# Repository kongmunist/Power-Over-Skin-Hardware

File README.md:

# Hi, welcome to the Power-over-Skin Repo

This repository contains the PCB files for the receiver board from the ACM UIST paper ["Power-over-Skin: Full-Body Wearables Powered By Intra-Body RF Energy"](https://dl.acm.org/doi/10.1145/3654777.3676394)

# BOM for receiver
You can assume all parts are generic unless mentioned below:

- R1-R7: Voltage setting resistors, should be 1% or better

- L2, L3: buck/boost inductors for the BQ25570. Should handle >200mA saturation current according to BQ25570 datasheet, but we're using low currents so you would probably get away with lower values. We used CB2518T100K and BRC2518T220K

- C4: Anything >100uF will do. I'm using the F950J107MPAAQ2, it is the only one that's quite so small, but it's also very DC-leaky

- L1: Should have a self-resonant frequency over 200 MHz in order to accomodate incoming square wave harmonics. 
- C9: Should be NP0, with a Vmax 10V or better

# Transmitter
In our experiments, we used a benchtop transmitter and a wearable one to generate 40 MHz square waves. These were passed through an impedance-matching network to couple into the body. The values we used were: first 20pF in series, then 820nH to ground. 

The 20pF should be NP0 with a voltage rating higher than the 40MHz you're sending into it. We used this inductor [(L-15FR82JV4E)](https://www.mouser.com/ProductDetail/Johanson-Technology/L-15FR82JV4E?qs=N%252Bgu1CRRfTPf9IhMOTDbHA%3D%3D) but anything with a self-resonant frequency >200 MHz should work. 

# Matching for other frequencies
The RF component values are all tuned for 40 MHz and human skin impedance — if you'd like to use another frequency, you'll have to resimulate the circuit. 

# Further questions?
Feel free to email Andy with any questions!

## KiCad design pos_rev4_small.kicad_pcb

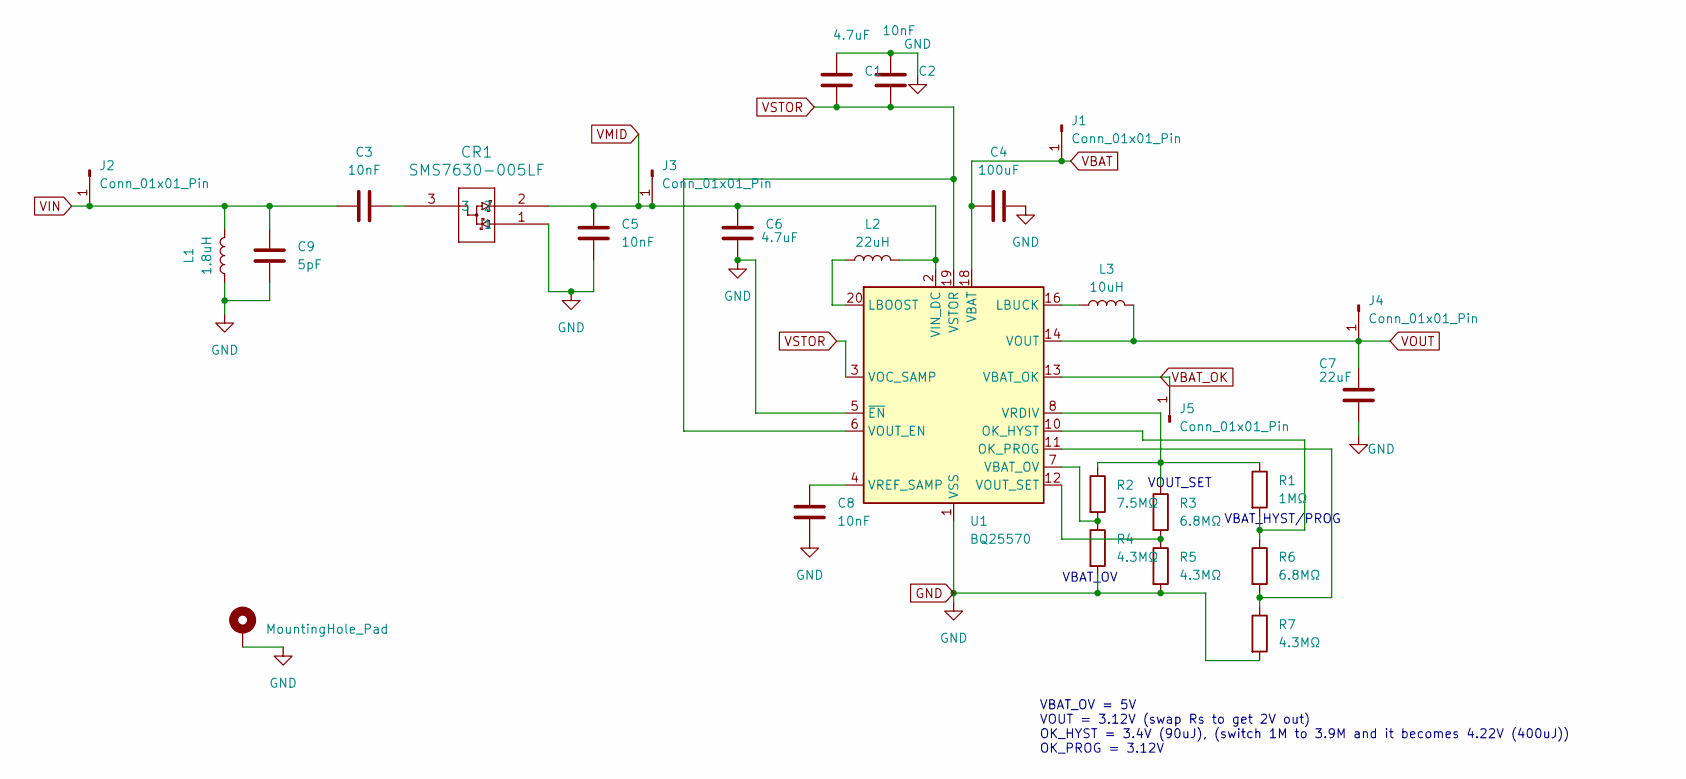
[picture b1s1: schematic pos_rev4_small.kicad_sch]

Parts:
C1, C6: 4.7uF; C_0402_1005Metric
C2, C3, C5, C8: 10nF; C_0402_1005Metric
C4: 100uF; C_0805_2012Metric
C7: 22uF; C_0603_1608Metric
C9: 5pF; C_0402_1005Metric
CR1: SMS7630-005LF; SOT-23_SKY
H1: MountingHole_Pad; TestPoint_Pad_D1.0mm
J1, J2, J3, J4, J5: Conn_01x01_Pin; TestPoint_Pad_D1.0mm
L1: 1.8uH; L_0805_2012Metric
L2: 22uH; L_1008_2520Metric
L3: 10uH; L_0805_2012Metric
R1: 1MΩ; R_0402_1005Metric
R2: 7.5MΩ; R_0402_1005Metric
R3, R6: 6.8MΩ; R_0402_1005Metric
R4, R5, R7: 4.3MΩ; R_0402_1005Metric
U1: BQ25570; QFN-20-1EP_3.5x3.5mm_P0.5mm_EP2x2mm

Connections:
GND: C1.1, C2.1, C4.2, C5.1, C6.2, C7.2, C8.2, C9.1, CR1.1, H1.1, L1.2, R4.2, R5.2, R7.2, U1.1 (VSS), U1.5 (~EN), U1.9 (VSS), U1.15 (VSS), U1.17 (VSS), U1.21 (VSS)
unnamed: C3.2, CR1.3
unnamed: L2.1, U1.20 (LBOOST)
unnamed: L3.1, U1.16 (LBUCK)
unnamed: R1.2, R6.1, U1.10 (OK_HYST)
unnamed: R6.2, R7.1, U1.11 (OK_PROG)
unnamed: R2.2, R4.1, U1.7 (VBAT_OV)
unnamed: R3.2, R5.1, U1.12 (VOUT_SET)
unnamed: R1.1, R2.1, R3.1, U1.8 (VRDIV)
unnamed: C8.1, U1.4 (VREF_SAMP)
VBAT: C4.1, J1.1, U1.18 (VBAT)
VBAT_OK: J5.1, U1.13 (VBAT_OK)
VIN: C3.1, C9.2, J2.1, L1.1
VMID: C5.2, C6.1, CR1.2, J3.1, L2.2, U1.2 (VIN_DC)
VOUT: C7.1, J4.1, L3.2, U1.14 (VOUT)
VSTOR: C1.2, C2.2, U1.3 (VOC_SAMP), U1.6 (VOUT_EN), U1.19 (VSTOR)

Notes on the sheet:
VOUT_SET
VBAT_HYST/PROG
VBAT_OV
VBAT_OV = 5V VOUT = 3.12V (swap Rs to get 2V out) OK_HYST = 3.4V (90uJ), (switch 1M to 3.9M and it becomes 4.22V (400uJ)) OK_PROG = 3.12V

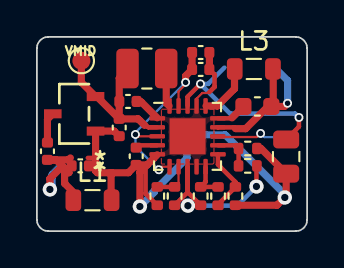
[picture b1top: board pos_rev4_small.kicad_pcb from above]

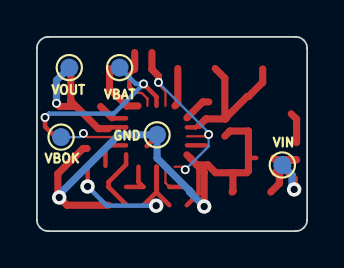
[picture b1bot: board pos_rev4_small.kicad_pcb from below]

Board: 2 copper layers, 15.0 x 10.8 mm, 27 parts (5 on the bottom side), 16 nets.

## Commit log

2024-07-12 init
2024-10-29 added readme, updated values.
2024-10-29 updated image
2025-01-04 updated pdf to have accurate RX LC values
